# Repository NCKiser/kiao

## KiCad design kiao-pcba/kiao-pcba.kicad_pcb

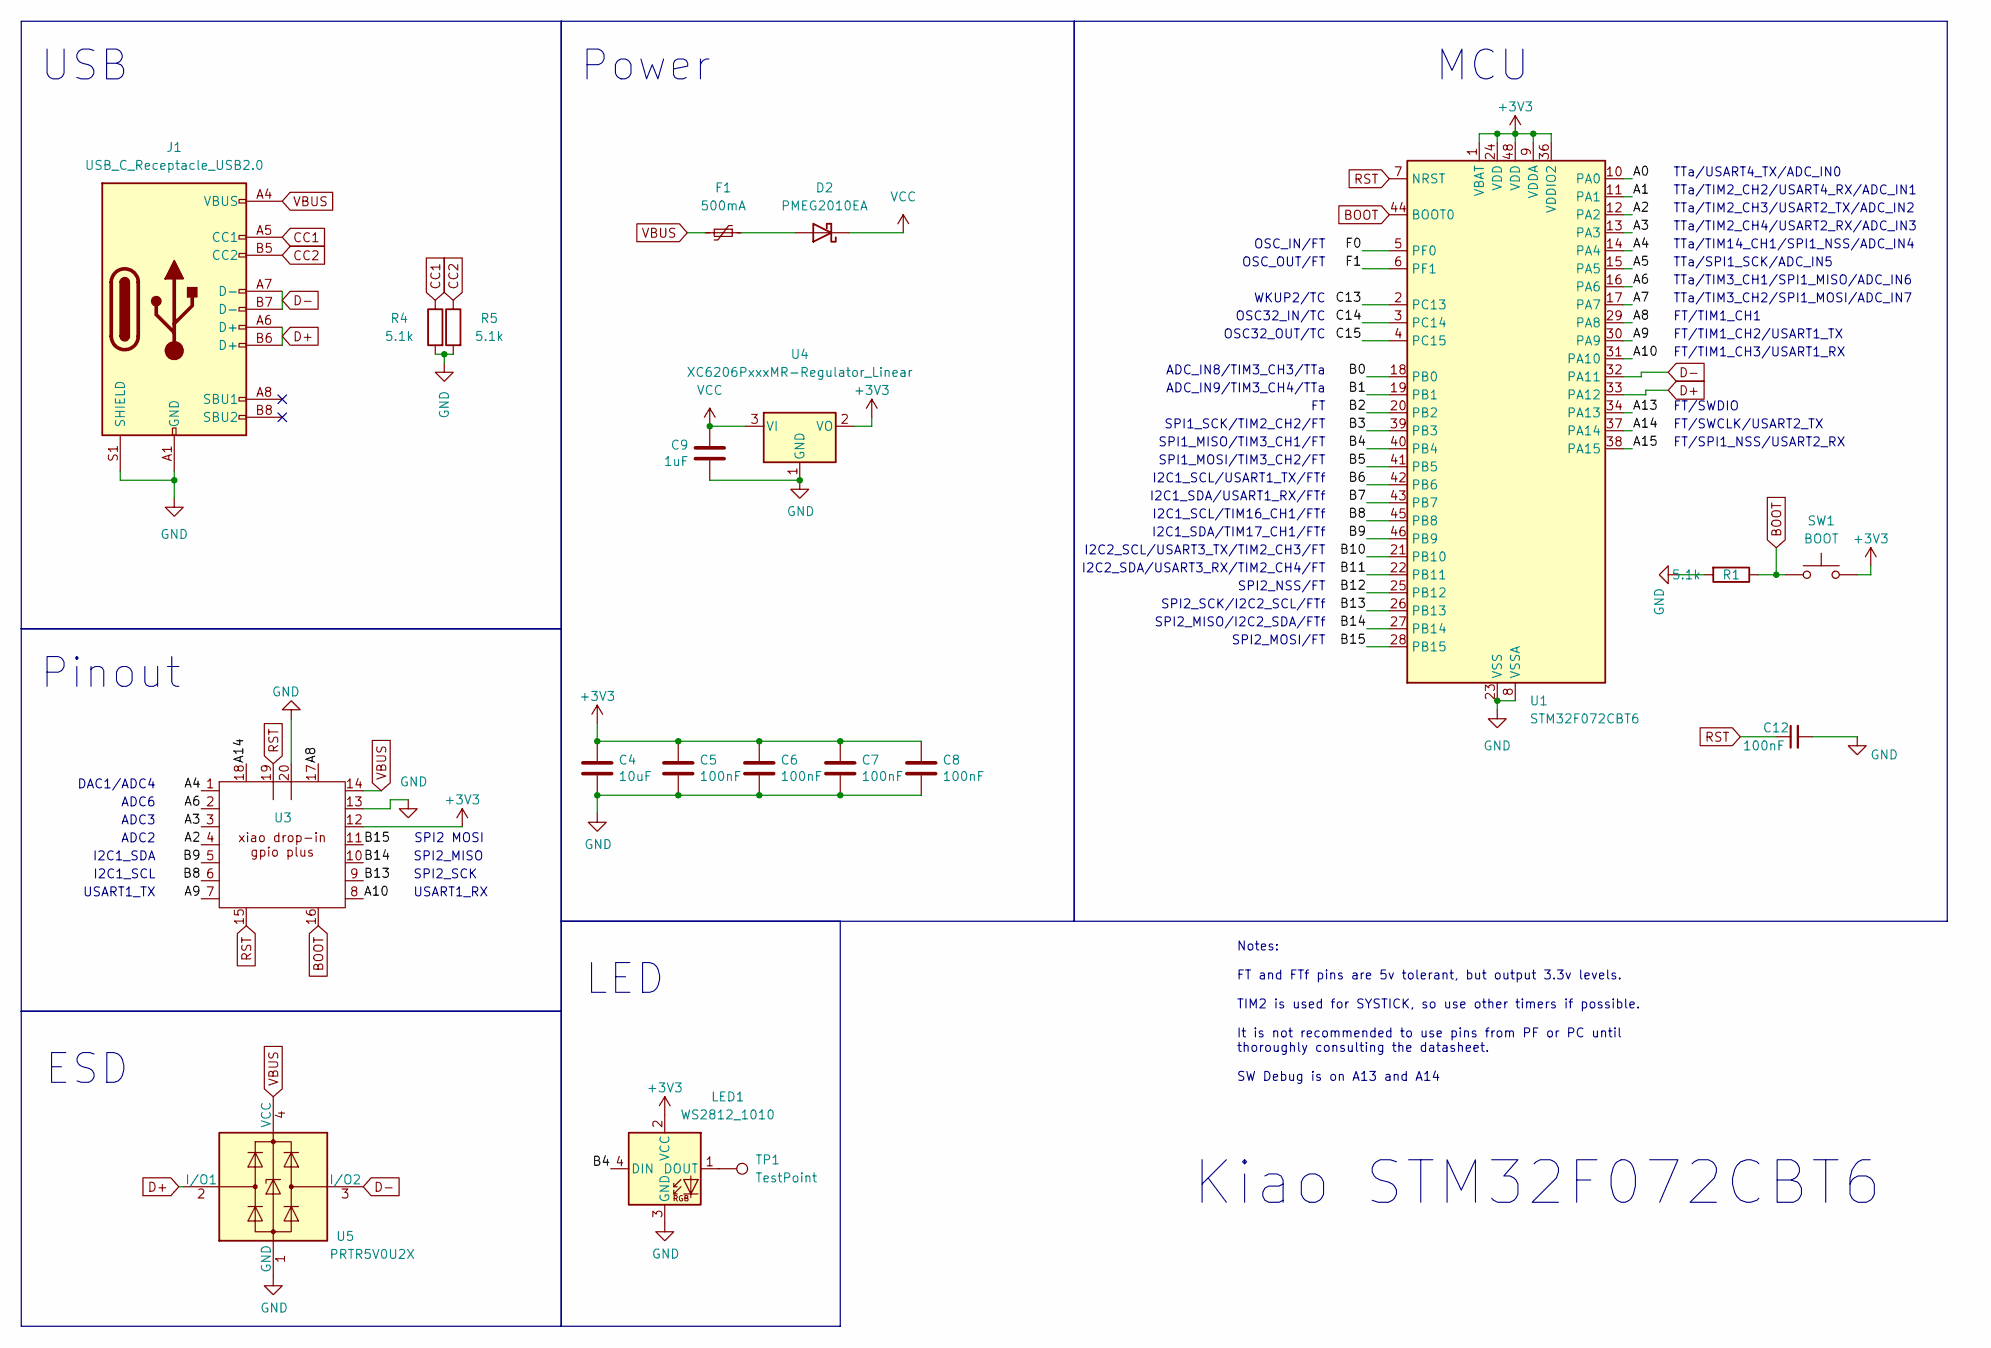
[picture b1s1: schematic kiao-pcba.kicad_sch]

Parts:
C4: 10uF; C_0402_1005Metric; LCSC C307331
C5, C6, C7, C8, C12: 100nF; C_0402_1005Metric; LCSC C307331
C9: 1uF; C_0402_1005Metric; LCSC C307331
D2: PMEG2010EA; D_0402_1005Metric; LCSC C2837790
F1: 500mA; Fuse_0402_1005Metric; LCSC C210357
J1: USB_C_Receptacle_USB2.0; USB_C_Receptacle_HRO_TYPE-C-31-M-12; JLCPCB_CORRECTION 0; -1.35; 0
LED1: WS2812_1010
R1: 5.1k; R_0402_1005Metric
R4, R5: 5.1k; R_0402_1005Metric; LCSC C25905
SW1: BOOT; SW_Push_SPST_NO_Alps_SKRK; LCSC C115357
TP1: TestPoint; TestPoint_THTPad_D1.0mm_Drill0.5mm
U1: STM32F072CBT6; LQFP-48_7x7mm_P0.5mm; JlcRotOffset 90
U3: xiao_drop-in_gpio_usb_no_cutout; xiao_drop-in_gpio_plus_4_castellated
U4: XC6206PxxxMR-Regulator_Linear; SOT-23; LCSC C5446
U5: PRTR5V0U2X; SOT-143; LCSC C2827688

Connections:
+3V3: C4.1, C5.1, C6.1, C7.1, C8.1, LED1.2 (VCC), SW1.2, U1.1 (VBAT), U1.9 (VDDA), U1.24 (VDD), U1.36 (VDDIO2), U1.48 (VDD), U3.12, U4.2 (VO)
/A0: U1.10 (PA0)
/A1: U1.11 (PA1)
/A2: U1.12 (PA2), U3.4
/A3: U1.13 (PA3), U3.3
/A4: U1.14 (PA4), U3.1
/A5: U1.15 (PA5)
/A6: U1.16 (PA6), U3.2
/A7: U1.17 (PA7)
/A8: U1.29 (PA8), U3.17
/A9: U1.30 (PA9), U3.7
/A10: U1.31 (PA10), U3.8
/A13: U1.34 (PA13)
/A14: U1.37 (PA14), U3.18
/A15: U1.38 (PA15)
/B0: U1.18 (PB0)
/B1: U1.19 (PB1)
/B2: U1.20 (PB2)
/B3: U1.39 (PB3)
/B4: LED1.4 (DIN), U1.40 (PB4)
/B5: U1.41 (PB5)
/B6: U1.42 (PB6)
/B7: U1.43 (PB7)
/B8: U1.45 (PB8), U3.6
/B9: U1.46 (PB9), U3.5
/B10: U1.21 (PB10)
/B11: U1.22 (PB11)
/B12: U1.25 (PB12)
/B13: U1.26 (PB13), U3.9
/B14: U1.27 (PB14), U3.10
/B15: U1.28 (PB15), U3.11
/C13: U1.2 (PC13)
/C14: U1.3 (PC14)
/C15: U1.4 (PC15)
/F0: U1.5 (PF0)
/F1: U1.6 (PF1)
BOOT: R1.1, SW1.1, U1.44 (BOOT0), U3.16
CC1: J1.A5 (CC1), R4.1
CC2: J1.B5 (CC2), R5.1
D+: J1.A6 (D+), J1.B6 (D+), U1.33 (PA12), U5.2 (I/O1)
D-: J1.A7 (D-), J1.B7 (D-), U1.32 (PA11), U5.3 (I/O2)
GND: C4.2, C5.2, C6.2, C7.2, C8.2, C9.2, C12.2, J1.A1 (GND), J1.A12 (GND), J1.B1 (GND), J1.B12 (GND), J1.S1 (SHIELD), LED1.3 (GND), R1.2, R4.2, R5.2, U1.8 (VSSA), U1.23 (VSS), U1.35 (VSS), U1.47 (VSS), U3.13, U3.20, U4.1 (GND), U5.1 (GND)
unnamed: D2.2 (A), F1.1
unnamed: LED1.1 (DOUT), TP1.1
RST: C12.1, U1.7 (NRST), U3.15, U3.19
VBUS: F1.2, J1.A4 (VBUS), J1.A9 (VBUS), J1.B4 (VBUS), J1.B9 (VBUS), U3.14, U5.4 (VCC)
VCC: C9.1, D2.1 (K), U4.3 (VI)

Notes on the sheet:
LED
SPI2_MOSI/FT
I2C1_SDA
TTa/TIM2_CH3/USART2_TX/ADC_IN2
MCU
Kiao STM32F072CBT6
I2C1_SDA/USART1_RX/FTf
DAC1/ADC4
USB
ADC6
SPI2_SCK/I2C2_SCL/FTf
Notes: FT and FTf pins are 5v tolerant, but output 3.3v levels. TIM2 is used for SYSTICK, so use other timers if possible. It is not recommended to use pins from PF or PC until thoroughly consulting the datasheet. SW Debug is on A13 and A14
TTa/TIM3_CH2/SPI1_MOSI/ADC_IN7
FT/SWCLK/USART2_TX
SPI2_NSS/FT
TTa/TIM3_CH1/SPI1_MISO/ADC_IN6
ADC3
SPI2_MISO
ADC_IN9/TIM3_CH4/TTa
I2C1_SCL/TIM16_CH1/FTf
TTa/USART4_TX/ADC_IN0
TTa/TIM14_CH1/SPI1_NSS/ADC_IN4
I2C1_SDA/TIM17_CH1/FTf
TTa/SPI1_SCK/ADC_IN5
WKUP2/TC
OSC_IN/FT
TTa/TIM2_CH4/USART2_RX/ADC_IN3
USART1_TX
SPI2_MISO/I2C2_SDA/FTf
FT/TIM1_CH1
Power
SPI1_MOSI/TIM3_CH2/FT
FT/SWDIO
OSC32_OUT/TC
SPI2_SCK
ESD
TTa/TIM2_CH2/USART4_RX/ADC_IN1
I2C2_SDA/USART3_RX/TIM2_CH4/FT
FT/TIM1_CH2/USART1_TX
SPI1_SCK/TIM2_CH2/FT

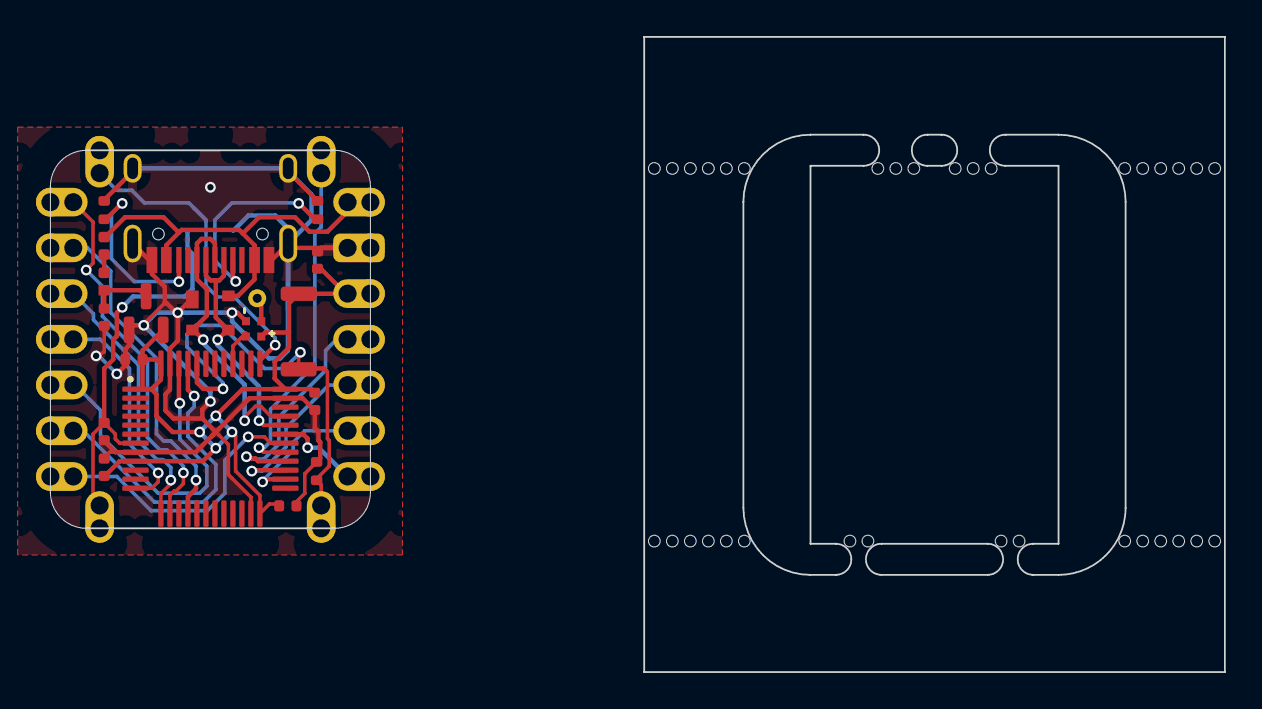
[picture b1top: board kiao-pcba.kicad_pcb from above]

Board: 2 copper layers, 65.2 x 35.3 mm, 20 parts (0 on the bottom side), 26 nets.

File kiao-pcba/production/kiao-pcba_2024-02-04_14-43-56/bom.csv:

Designator,Footprint,Quantity,Value,LCSC Part #
"C12, C5, C6, C7, C8",402,5,100nF,C1525 
C4,402,1,10uF,C15525 
C9,402,1,1uF,C52923 
D2,402,1,PMEG2010EA,C2837790
F1,402,1,500mA,C914087
J1,USB_C_Receptacle_HRO_TYPE-C-31-M-12,1,USB_C_Receptacle_USB2.0,C165948 
LED1,WS2812_1010,1,WS2812_1010,C5349953 
"R1, R4, R5",402,3,5.1k,C25905 
SW1,SW_Push_SPST_NO_Alps_SKRK,1,BOOT,C720477 
U1,LQFP-48_7x7mm_P0.5mm,1,STM32F072CBT6,C81720 
U4,SOT-23,1,XC6206PxxxMR-Regulator_Linear,C5446 
U5,SOT-143,1,PRTR5V0U2X,C2827688

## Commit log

2024-02-04 Changes pinout, half-panel, gerbers. Proto'd
2024-02-06 separated panelization
